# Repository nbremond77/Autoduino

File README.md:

# Autoduino

Arduino UNO shield to interface the I/O modules of A4 Technology // Autoduino est un bouclier pour Arduino Uno qui permet de piloter les maquettes A4 Technology utilisées pour l'enseignement de la technologie.

Exemples de maquettes:

http://www.a4.fr/maquette-motorisee-programmable-portail-1-battant-version-kit.html

http://www.a4.fr/banc-d-essai-eclairage-domestique-autolumi-version-kit.html

http://www.a4.fr/autoalarme-maquette-experimentale-d-un-systeme-d-alarme-kit.html

Vous trouverez sur ce site, les fichiers relatif à la carte électronique, et les développements logiciels associés.

# Introduction
Le bouclier Autoduino permet de piloter les maquettes A4 technology grâce à un Arduino UNO. Pour cela, le bouclier est équipé de 
- 16 connecteurs Jack 2.5mm permettant la connection des capteurs et actionneurs de la maquette, équipé de LED pour indiquer l'état de l'entrée ou de la sortie.
- 2 connecteurs jack 2.5mm pour deux moteurs DC,
- 2 LED RGB adressables (type WS2812B),
- 1 encodeur/push,
- quelques connecteurs supplémentaires permettant de connecter des capteurs/actionneurs plus évolués UEXT (I2C, SPI, Serial...) ou I2C pour un écran LCD (non testé) par exemple,
- 1 connecteur pour un module BlueTooth,
- 1 convertisseur Step/Up permettant d'alimenter la carte et l'Arduino avec deux piles de 1.5V, ou avec un accumulateur 3.7V.

Pour supporter le grand nombre d'entrées/sorties, il a été nécessaire d'utiliser un GPIO Expander (PCA9555). Celà implique l'utilisation d'une bibliothèque logiciel adaptée.
La programmation de l'Arduino peut se faire grâce à blockly@rDuino: http://technologiescollege.github.io/ qui inclus maintenant la bibliothèque adéquate.

A noter: Autoduino utilise des composants CMS et des composants traversants. Le cuircuit imprimé fait 100x100mm et est du type double-face.

# Note importante
Une nouvelle version de cet Autoduino est en préparation. La carte électronique sera plus simple (moins de connecteurs), et surtout, elle sera adaptée à un Arduino Due qui dispose de beaucoup plus d'entrées/sortie. Cela permettra d'éviter l'utilisation du GPIO Explander (PCA9555), ce qui simplifie grandement le logiciel.
De plus, l'Arduino Due fonctionne en 3.3V, ce qui simplifie l'utilisation de périphériques récents (Ecran tactile LCD...). Les moteurs resteront connectés au 5V.
Enfin, c'est un processeur 32 bits beaucoup plus performant que celui de l'Arduino Uno;

De plus, j'ai prévu quelques amélioration:
- Ajout de connecteurs Grove en plus des connecteurs jack 2.5mm, pour permettre une utilisation beaucoup plus polyvalente,
- Possibilité de connecter le module Bluetooth sur un RX/TX différent de celui connecté à l'USB,
- Ajouter une interface permettant de connecter un écran tactile LCD de 2.8 pouces.

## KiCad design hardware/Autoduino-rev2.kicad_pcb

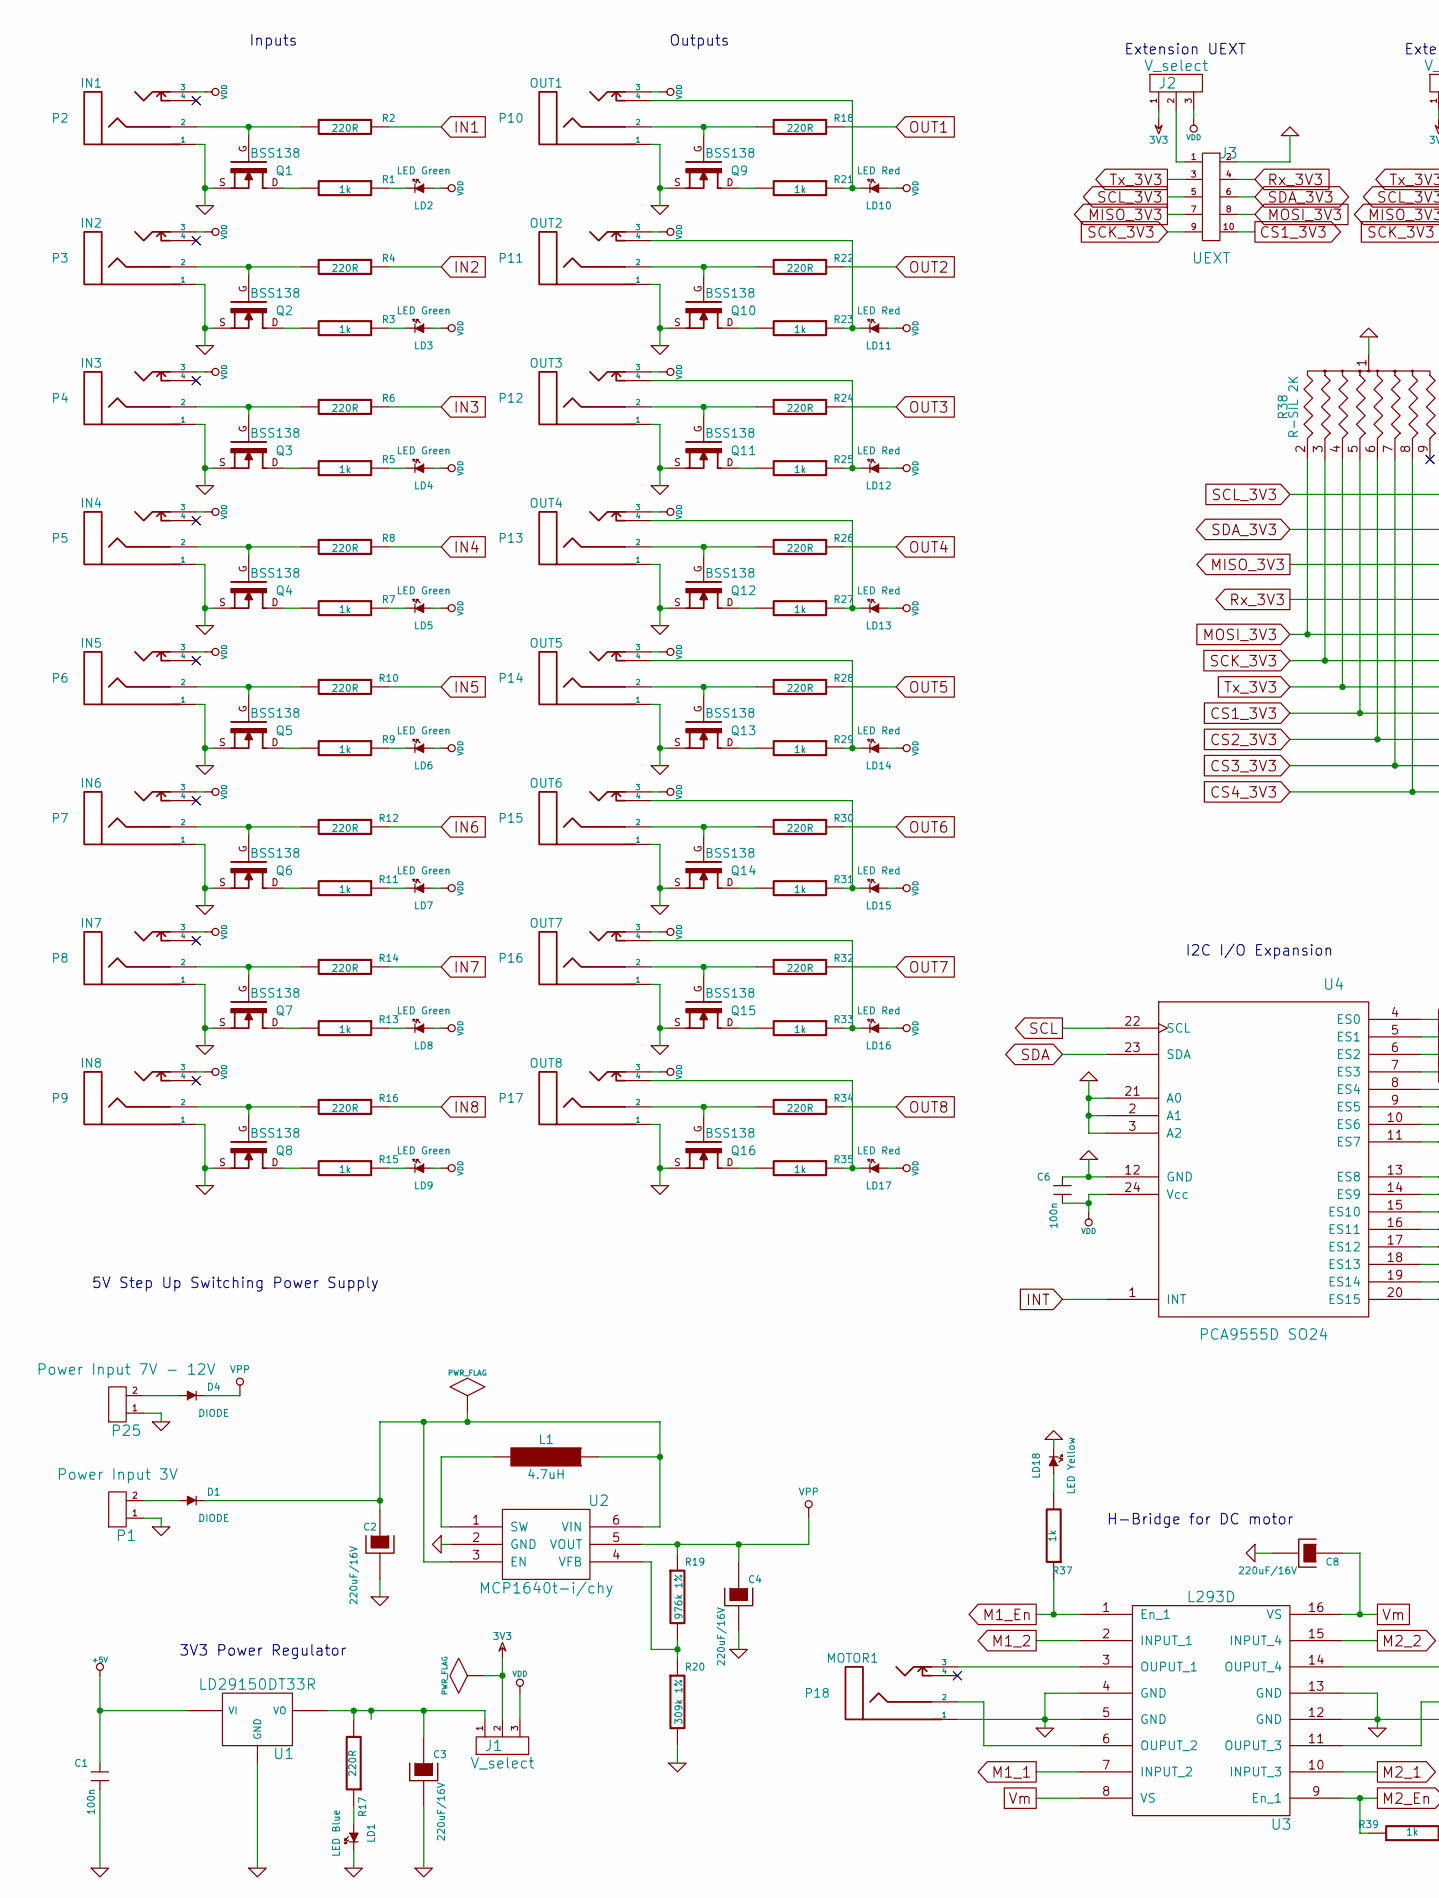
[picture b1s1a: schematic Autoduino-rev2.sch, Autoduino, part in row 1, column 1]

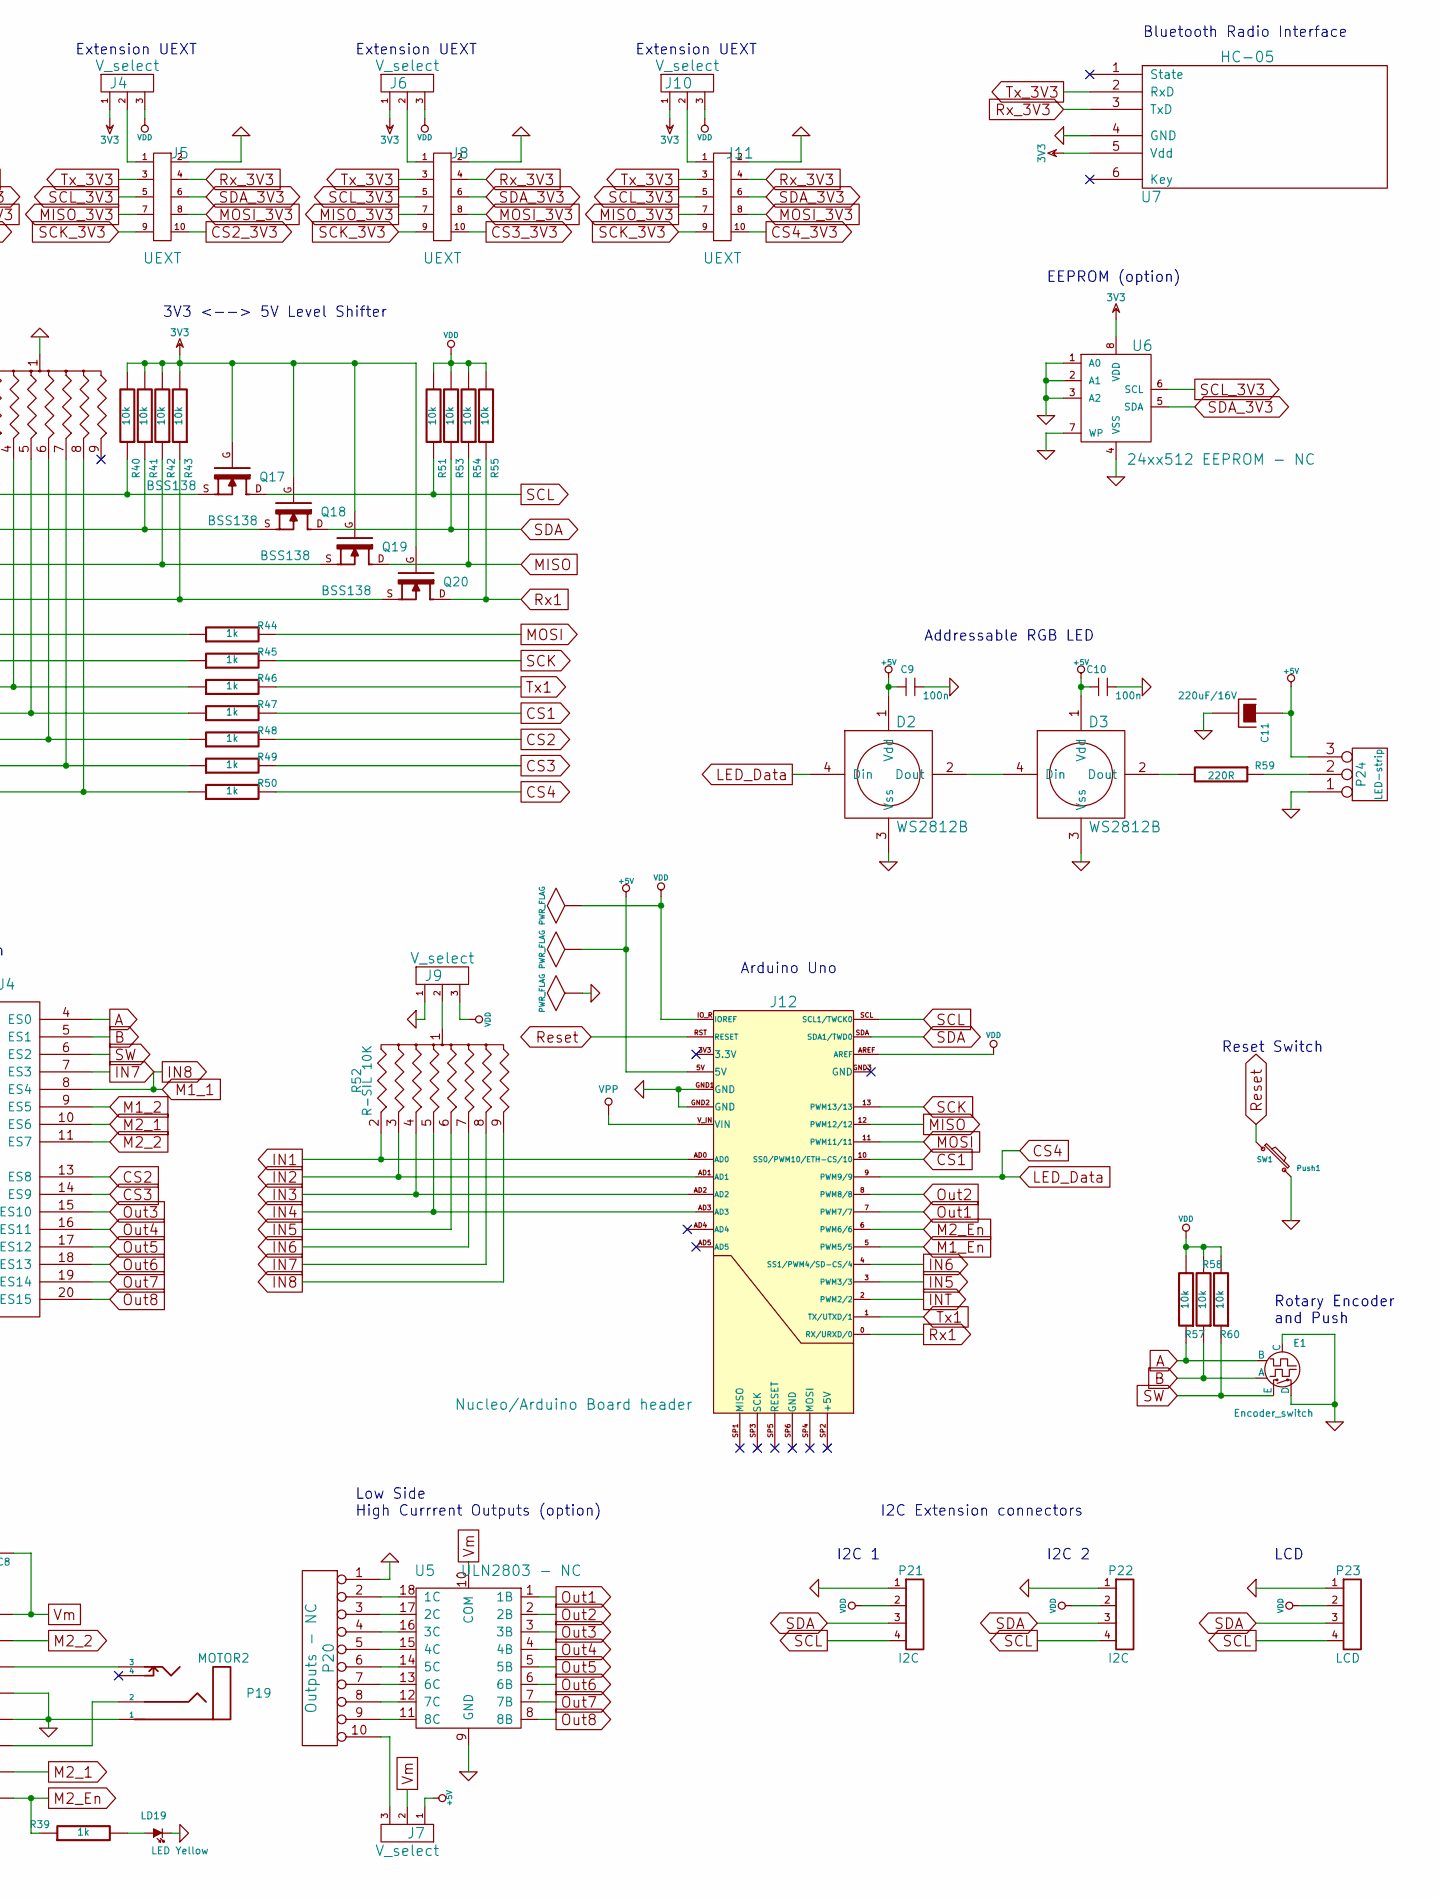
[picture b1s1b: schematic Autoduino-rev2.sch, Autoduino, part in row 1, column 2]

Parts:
C1, C6, C9, C10: 100n; C_0805
C2, C3, C4, C8, C11: 220uF/16V; c_elec_8x10
D1, D4: DIODE; Diode-MiniMELF_Handsoldering
D2, D3: WS2812B
E1: Encoder_switch; encoder_alps-ec12d
J1, J2, J4, J6, J7, J9, J10: V_select; Select
J3, J5, J8, J11: UEXT; Pin_Header_Straight_2x05
J12: Nucleo/Arduino Board header; ARDUINO_SHIELD
L1: 4.7uH; INDUCTOR_V
LD1: LED Blue; LED-3MM
LD2, LD3, LD4, LD5, LD6, LD7, LD8, LD9: LED Green; LED-3MM
LD10, LD11, LD12, LD13, LD14, LD15, LD16, LD17: LED Red; LED-3MM
LD18, LD19: LED Yellow; LED-3MM
P1: Power Input 3V; Pin_Header_Straight_1x02
P2: IN1; PC-208B-Jack2.5_Stereo
P3: IN2; PC-208B-Jack2.5_Stereo
P4: IN3; PC-208B-Jack2.5_Stereo
P5: IN4; PC-208B-Jack2.5_Stereo
P6: IN5; PC-208B-Jack2.5_Stereo
P7: IN6; PC-208B-Jack2.5_Stereo
P8: IN7; PC-208B-Jack2.5_Stereo
P9: IN8; PC-208B-Jack2.5_Stereo
P10: OUT1; PC-208B-Jack2.5_Stereo
P11: OUT2; PC-208B-Jack2.5_Stereo
P12: OUT3; PC-208B-Jack2.5_Stereo
P13: OUT4; PC-208B-Jack2.5_Stereo
P14: OUT5; PC-208B-Jack2.5_Stereo
P15: OUT6; PC-208B-Jack2.5_Stereo
P16: OUT7; PC-208B-Jack2.5_Stereo
P17: OUT8; PC-208B-Jack2.5_Stereo
P18: MOTOR1; PC-208B-Jack2.5_Stereo
P19: MOTOR2; PC-208B-Jack2.5_Stereo
P20: Outputs - NC; Pin_Header_Straight_2x05
P21, P22: I2C; Pin_Header_Straight_1x04
P23: LCD; Pin_Header_Straight_1x04
P24: LED-strip; Pin_Header_Straight_1x03
P25: Power Input 7V - 12V; Pin_Header_Straight_1x02
Q1, Q2, Q3, Q4, Q5, Q6, Q7, Q8, Q9, Q10, Q11, Q12, Q13, Q14, Q15, Q16, Q17, Q18, Q19, Q20: BSS138; SOT23_FET
R1, R3, R5, R7, R9, R11, R13, R15, R21, R23, R25, R27, R29, R31, R33, R35, R37, R39, R44, R45, R46, R47, R48, R49, R50: 1k; R_0805
R2, R4, R6, R8, R10, R12, R14, R16, R17, R18, R22, R24, R26, R28, R30, R32, R34, R59: 220R; R_0805
R19: 976k 1%; R_0805
R20: 309k 1%; R_0805
R38: R-SIL 2K; r_pack8
R40, R41, R42, R43, R51, R53, R54, R55, R57, R58, R60: 10k; R_0805
R52: R-SIL 10K; r_pack8
SW1: Push1; SW_PUSHBUTTON_PTH
U1: LD29150DT33R; DPAK
U2: MCP1640t-i/chy; sot23-6
U3: L293D; DIP-16__300
U4: PCA9555D SO24; SOIC-24_7.5x15.4mm_Pitch1.27mm
U5: ULN2803 - NC; DIP-18__300
U6: 24xx512 EEPROM - NC; so-8
U7: HC-05; Pin_Header_Angled_1x06

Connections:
3V3: J1.2, J2.1, J4.1, J6.1, J10.1, Q17.G, Q18.G, Q19.G, Q20.G, R40.2, R41.2, R42.2, R43.2, U6.8 (VDD), U7.5 (Vdd)
+5V: C1.1, C9.1, C10.1, C11.1, D2.1 (Vdd), D3.1 (Vdd), J7.1, J12.5V, P24.3, U1.1 (VI)
A: E1.3 (B), R57.1, U4.4 (ES0)
B: E1.1 (A), R58.1, U4.5 (ES1)
CS1: J12.10 (SS0/PWM10/ETH-CS/10), R47.2
CS1_3V3: J3.10, R38.5, R47.1
CS2: R48.2, U4.13 (ES8)
CS2_3V3: J5.10, R38.6, R48.1
CS3: R49.2, U4.14 (ES9)
CS3_3V3: J8.10, R38.7, R49.1
CS4_3V3: J11.10, R38.8, R50.1
GND: C1.2, C2.2, C3.2, C4.2, C6.1, C8.2, C9.2, C10.2, C11.2, D2.3 (Vss), D3.3 (Vss), E1.2 (C), E1.5 (D), J3.2, J5.2, J8.2, J9.1, J11.2, J12.GND1 (GND), J12.GND2 (GND), LD1.2 (K), LD18.2 (K), LD19.2 (K), P1.1, P2.1, P3.1, P4.1, P5.1, P6.1, P7.1, P8.1, P9.1, P10.1, P11.1, P12.1, P13.1, P14.1, P15.1, P16.1, P17.1, P18.1, P19.1, P20.1, P21.1, P22.1, P23.1, P24.1, P25.1, Q1.S, Q2.S, Q3.S, Q4.S, Q5.S, Q6.S, Q7.S, Q8.S, Q9.S, Q10.S, Q11.S, Q12.S, Q13.S, Q14.S, Q15.S, Q16.S, R20.2, R38.1, SW1.2, U1.2 (GND), U2.2 (GND), U3.4 (GND), U3.5 (GND), U3.12 (GND), U3.13 (GND), U4.2 (A1), U4.3 (A2), U4.12 (GND), U4.21 (A0), U5.9 (GND), U6.1 (A0), U6.2 (A1), U6.3 (A2), U6.4 (VSS), U6.7 (WP), U7.4 (GND)
IN1: J12.AD0, R2.1, R52.2
IN2: J12.AD1, R4.1, R52.3
IN3: J12.AD2, R6.1, R52.4
IN4: J12.AD3, R8.1, R52.5
IN5: J12.3 (PWM3/3), R10.1, R52.6
IN6: J12.4 (SS1/PWM4/SD-CS/4), R12.1, R52.7
IN7: R14.1, R52.8, U4.7 (ES3)
IN8: R16.1, R52.9, U3.7 (INPUT_2), U4.8 (ES4)
INT: J12.2 (PWM2/2), U4.1 (INT)
LED_Data: D2.4 (Din), J12.9 (PWM9/9), R50.2
M1_2: U3.2 (INPUT_1), U4.9 (ES5)
M1_En: J12.5 (PWM5/5), R37.1, U3.1 (En_1)
M2_1: U3.10 (INPUT_3), U4.10 (ES6)
M2_2: U3.15 (INPUT_4), U4.11 (ES7)
M2_En: J12.6 (PWM6/6), R39.1, U3.9 (En_1)
MISO: J12.12 (PWM12/12), Q19.D, R54.1
MISO_3V3: J3.7, J5.7, J8.7, J11.7, Q19.S, R42.1
MOSI: J12.11 (PWM11/11), R44.2
MOSI_3V3: J3.8, J5.8, J8.8, J11.8, R38.2, R44.1
unnamed: C2.1, D1.2 (K), L1.1, U2.3 (EN), U2.6 (VIN)
unnamed: C3.1, J1.1, R17.2, U1.3 (VO)
unnamed: D1.1 (A), P1.2
unnamed: D2.2 (Dout), D3.4 (Din)
unnamed: D3.2 (Dout), R59.2
unnamed: D4.1 (A), P25.2
unnamed: J2.2, J3.1
unnamed: J4.2, J5.1
unnamed: J6.2, J8.1
unnamed: J7.3, P20.10
unnamed: J9.2, R52.1
unnamed: J10.2, J11.1
unnamed: L1.2, U2.1 (SW)
unnamed: LD1.1 (A), R17.1
unnamed: LD2.2 (K), R1.1
unnamed: LD3.2 (K), R3.1
unnamed: LD4.2 (K), R5.1
unnamed: LD5.2 (K), R7.1
unnamed: LD6.2 (K), R9.1
unnamed: LD7.2 (K), R11.1
unnamed: LD8.2 (K), R13.1
unnamed: LD9.2 (K), R15.1
unnamed: LD10.2 (K), P10.4, R21.1
unnamed: LD11.2 (K), P11.4, R23.1
unnamed: LD12.2 (K), P12.4, R25.1
unnamed: LD13.2 (K), P13.4, R27.1
unnamed: LD14.2 (K), P14.4, R29.1
unnamed: LD15.2 (K), P15.4, R31.1
unnamed: LD16.2 (K), P16.4, R33.1
unnamed: LD17.2 (K), P17.4, R35.1
unnamed: LD18.1 (A), R37.2
unnamed: LD19.1 (A), R39.2
unnamed: P2.2, Q1.G, R2.2
unnamed: P3.2, Q2.G, R4.2
unnamed: P4.2, Q3.G, R6.2
unnamed: P5.2, Q4.G, R8.2
unnamed: P6.2, Q5.G, R10.2
unnamed: P7.2, Q6.G, R12.2
unnamed: P8.2, Q7.G, R14.2
unnamed: P9.2, Q8.G, R16.2
unnamed: P10.2, Q9.G, R18.2
unnamed: P11.2, Q10.G, R22.2
unnamed: P12.2, Q11.G, R24.2
unnamed: P13.2, Q12.G, R26.2
unnamed: P14.2, Q13.G, R28.2
unnamed: P15.2, Q14.G, R30.2
unnamed: P16.2, Q15.G, R32.2
unnamed: P17.2, Q16.G, R34.2
unnamed: P18.2, U3.6 (OUPUT_2)
unnamed: P18.3, U3.3 (OUPUT_1)
unnamed: P19.2, U3.11 (OUPUT_3)
unnamed: P19.3, U3.14 (OUPUT_4)
unnamed: P20.2, U5.18 (1C)
unnamed: P20.3, U5.17 (2C)
unnamed: P20.4, U5.16 (3C)
unnamed: P20.5, U5.15 (4C)
unnamed: P20.6, U5.14 (5C)
unnamed: P20.7, U5.13 (6C)
unnamed: P20.8, U5.12 (7C)
unnamed: P20.9, U5.11 (8C)
unnamed: P24.2 (PM), R59.1
unnamed: Q1.D, R1.2
unnamed: Q2.D, R3.2
unnamed: Q3.D, R5.2
unnamed: Q4.D, R7.2
unnamed: Q5.D, R9.2
unnamed: Q6.D, R11.2
unnamed: Q7.D, R13.2
unnamed: Q8.D, R15.2
unnamed: Q9.D, R21.2
unnamed: Q10.D, R23.2
unnamed: Q11.D, R25.2
unnamed: Q12.D, R27.2
unnamed: Q13.D, R29.2
unnamed: Q14.D, R31.2
unnamed: Q15.D, R33.2
unnamed: Q16.D, R35.2
unnamed: R19.2, R20.1, U2.4 (VFB)
OUT1: J12.7 (PWM7/7), R18.1, U5.1 (1B)
OUT2: J12.8 (PWM8/8), R22.1, U5.2 (2B)
OUT4: R26.1, U4.16 (ES11), U5.4 (4B)
OUT5: R28.1, U4.17 (ES12), U5.5 (5B)
OUT7: R32.1, U4.19 (ES14), U5.7 (7B)
OUT8: R34.1, U4.20 (ES15), U5.8 (8B)
Out3: R24.1, U4.15 (ES10), U5.3 (3B)
Out6: R30.1, U4.18 (ES13), U5.6 (6B)
Reset: J12.RST (RESET), SW1.1
Rx1: J12.0 (RX/URXD/0), Q20.D, R55.1
Rx_3V3: J3.4, J5.4, J8.4, J11.4, Q20.S, R43.1, U7.3 (TxD)
SCK: J12.13 (PWM13/13), R45.2
SCK_3V3: J3.9, J5.9, J8.9, J11.9, R38.3, R45.1
SCL: J12.SCL (SCL1/TWCK0), P21.4, P22.4, P23.4, Q17.D, R51.1, U4.22 (SCL)
SCL_3V3: J3.5, J5.5, J8.5, J11.5, Q17.S, R40.1, U6.6 (SCL)
SDA: J12.SDA (SDA1/TWD0), P21.3, P22.3, P23.3, Q18.D, R53.1, U4.23 (SDA)
SDA_3V3: J3.6, J5.6, J8.6, J11.6, Q18.S, R41.1, U6.5 (SDA)
SW: E1.4 (E), R60.1, U4.6 (ES2)
Tx1: J12.1 (TX/UTXD/1), R46.2
Tx_3V3: J3.3, J5.3, J8.3, J11.3, R38.4, R46.1, U7.2 (RxD)
VDD: C6.2, J1.3, J2.3, J4.3, J6.3, J9.3, J10.3, J12.AREF, J12.IO_R (IOREF), LD2.1 (A), LD3.1 (A), LD4.1 (A), LD5.1 (A), LD6.1 (A), LD7.1 (A), LD8.1 (A), LD9.1 (A), LD10.1 (A), LD11.1 (A), LD12.1 (A), LD13.1 (A), LD14.1 (A), LD15.1 (A), LD16.1 (A), LD17.1 (A), P2.3, P3.3, P4.3, P5.3, P6.3, P7.3, P8.3, P9.3, P10.3, P11.3, P12.3, P13.3, P14.3, P15.3, P16.3, P17.3, P21.2, P22.2, P23.2, R51.2, R53.2, R54.2, R55.2, R57.2, R58.2, R60.2, U4.24 (Vcc)
VPP: C4.1, D4.2 (K), J12.V_IN (VIN), R19.1, U2.5 (VOUT)
Vm: C8.1, J7.2, U3.8 (VS), U3.16 (VS), U5.10 (COM)

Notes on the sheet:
Extension UEXT
EEPROM (option)
5V Step Up Switching Power Supply
3V3 Power Regulator
Bluetooth Radio Interface
Low Side High Currrent Outputs (option)
3V3 <--> 5V Level Shifter
Addressable RGB LED
Arduino Uno
I2C I/O Expansion
H-Bridge for DC motor
LCD
Rotary Encoder and Push
Reset Switch
Inputs
Outputs
I2C Extension connectors
I2C 2
I2C 1

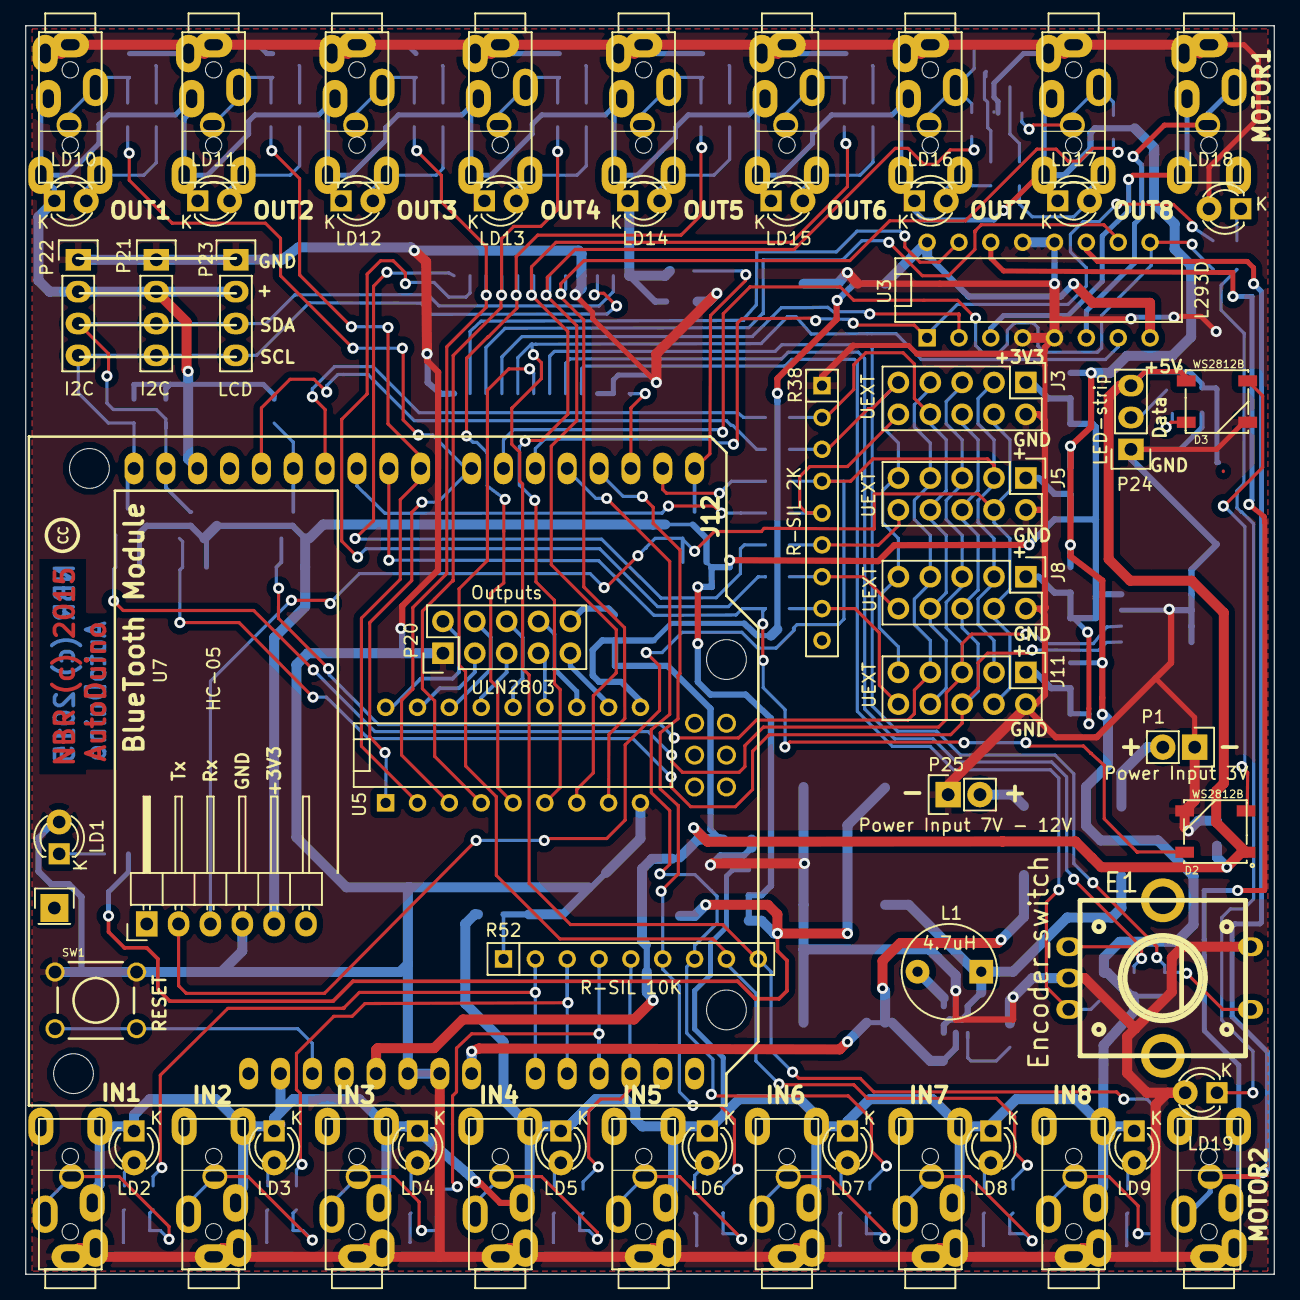
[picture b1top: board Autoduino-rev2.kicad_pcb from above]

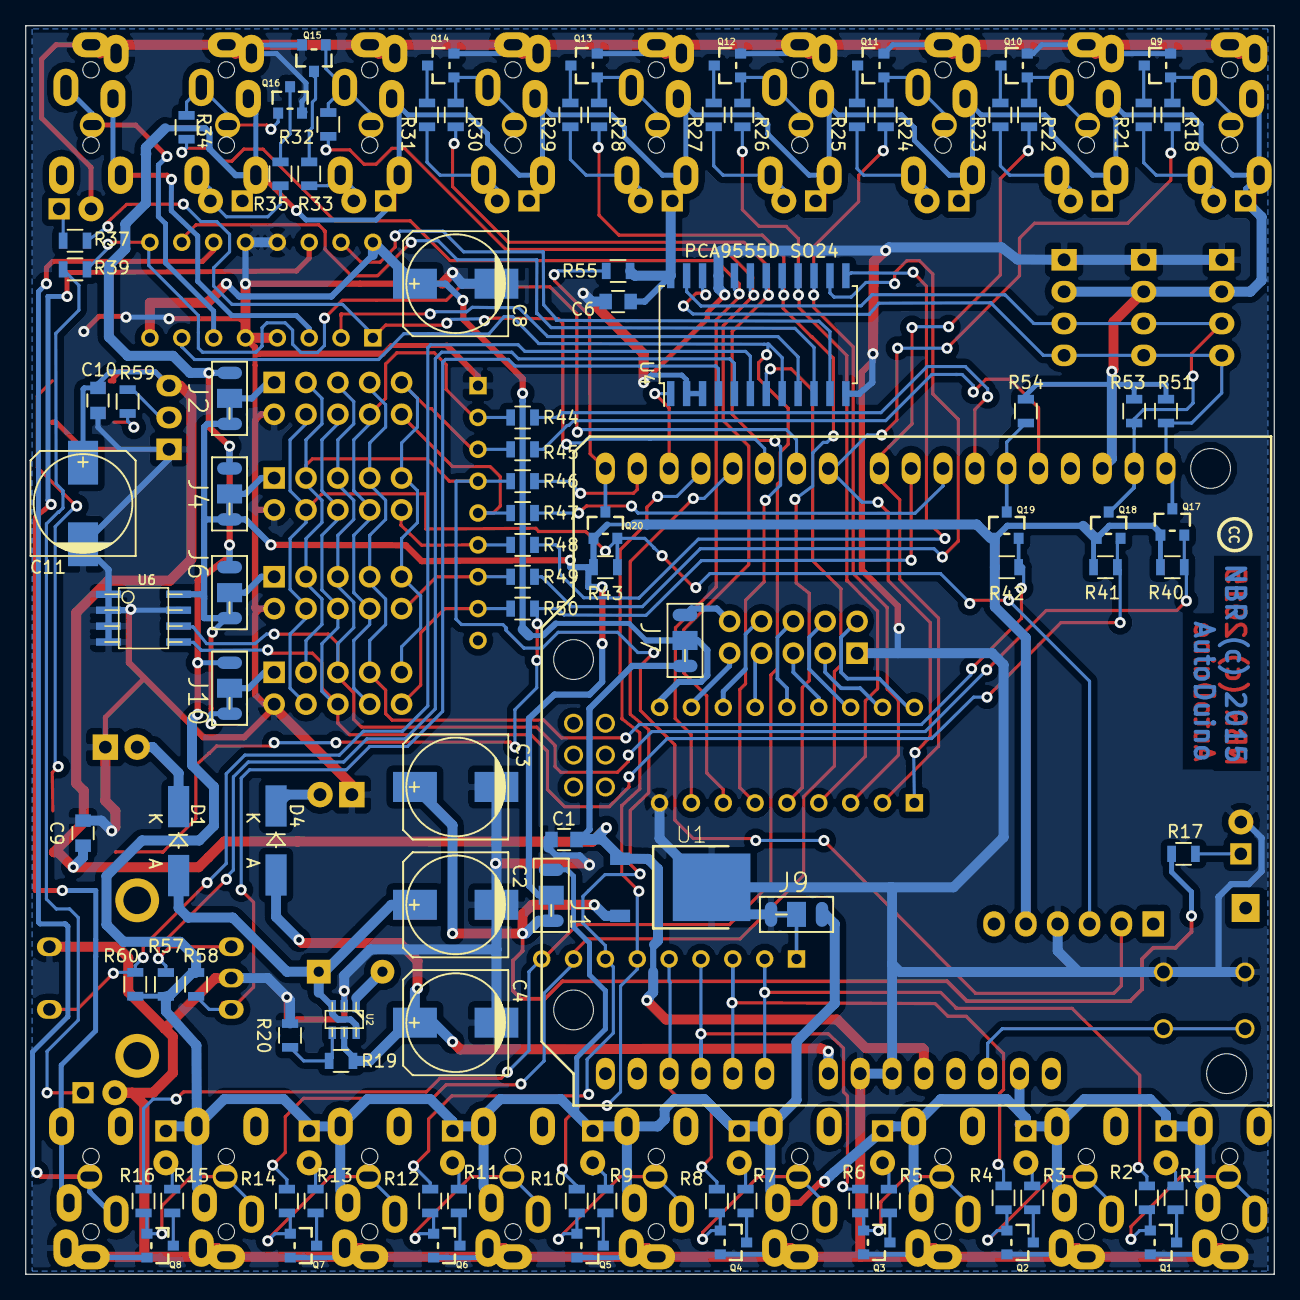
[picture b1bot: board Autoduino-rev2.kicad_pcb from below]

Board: 2 copper layers, 99.6 x 99.6 mm, 160 parts (99 on the bottom side), 132 nets.

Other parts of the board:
LOGO_CC: VAL**; LOGO_CC_2.8mm
LOGO_CC#2: VAL**; LOGO_CC_2.8mm
P0: Pin_Header_Straight_1x01

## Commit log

2016-04-25 Added files via upload
2016-04-25 Rename empty.txt to hardware/empty.txt
2016-04-25 Rename hardware/empty.txt to hardware/Output/empty.txt
2016-04-25 Rename empty.txt to Software/empty.txt
2016-04-25 Rename Software/autoduino.js to Software/blocks/autoduino.js
2016-04-25 Rename Software/blocks/empty.txt to Software/blocks/media/empty.txt
2016-04-25 Rename Software/generatempty.txt to Software/generators/empty.txt
2016-04-25 Rename Software/generators/empty.txt to Software/generators/arduino/empty.txt
2016-04-25 Rename empty.txt to lang/blocks/empty.txt
2016-04-25 Rename lang/blocks/fr.js to Software/lang/blocks/fr.js
2016-04-25 Rename lang/blocks/empty.txt to Software/lang/blocks/empty.txt
2016-04-25 Rename empty.txt to photos/empty.txt
2016-04-26 Rename Software/blocks/autoduino.js to Software/blocks/autoduino/autoduino.js
2016-04-26 Rename Software/blocks/media/empty.txt to Software/blocks/autoduino/media/empty.txt
2016-04-28 Rename Software/lang/blocks/code.js to Software/lang/code.js

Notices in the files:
hardware/Autoduino-rev2.kicad_pcb:
NBR (c) 2015
hardware/Autoduino-rev2.sch:
Open hardware Licence
